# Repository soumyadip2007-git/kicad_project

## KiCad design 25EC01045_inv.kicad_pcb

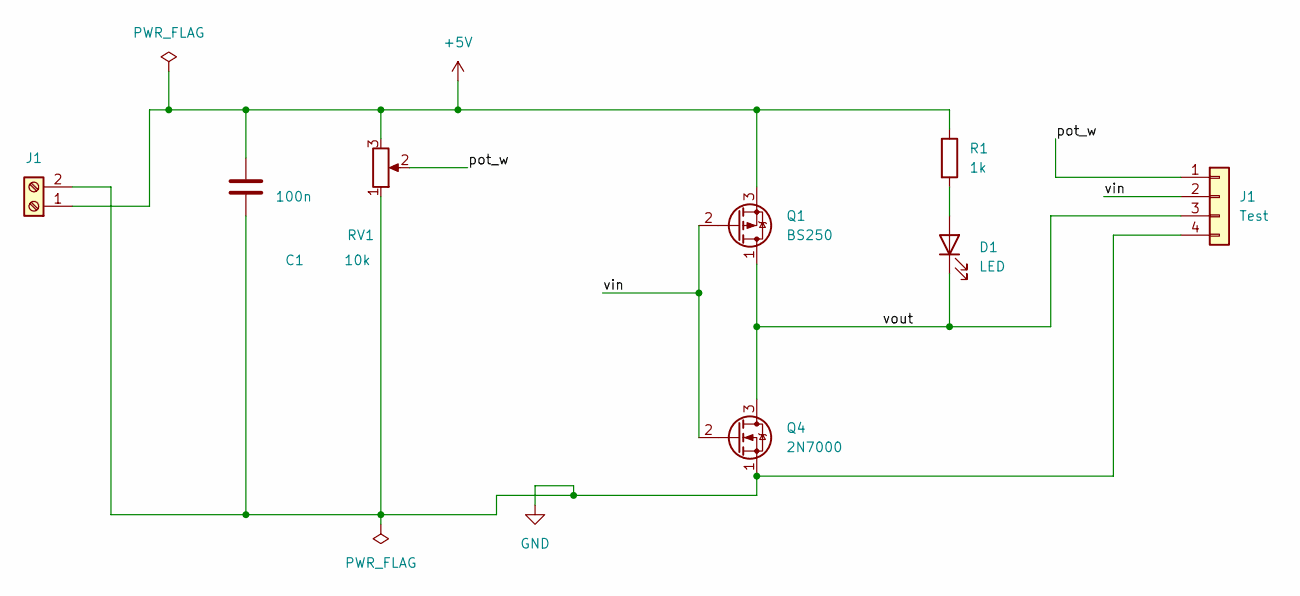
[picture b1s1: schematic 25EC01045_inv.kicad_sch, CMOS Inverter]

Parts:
C1: 100n; C_Disc_D5.0mm_W2.5mm_P5.00mm
D1: LED; LED_D3.0mm
J1: Test; PinHeader_1x04_P2.54mm_Vertical
J2: J1; TerminalBlock_Phoenix_MKDS-1,5-2-5.08_1x02_P5.08mm_Horizont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
Q1: BS250; TO-92_Inline
Q4: 2N7000; TO-92_Inline
R1: 1k; R_Axial_DIN0207_L6.3mm_D2.5mm_P10.16mm_Horizontal
RV1: 10k; Potentiometer_Bourns_3386P_Vertical

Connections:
+5V: C1.1, J2.1, Q1.3 (S), R1.1, RV1.3
/pot_w: J1.1, RV1.2
/vin: J1.2, Q1.2 (G), Q4.2 (G)
/vout: D1.1 (K), J1.3, Q1.1 (D), Q4.3 (D)
GND: C1.2, J1.4, J2.2, Q4.1 (S), RV1.1
unnamed: D1.2 (A), R1.2

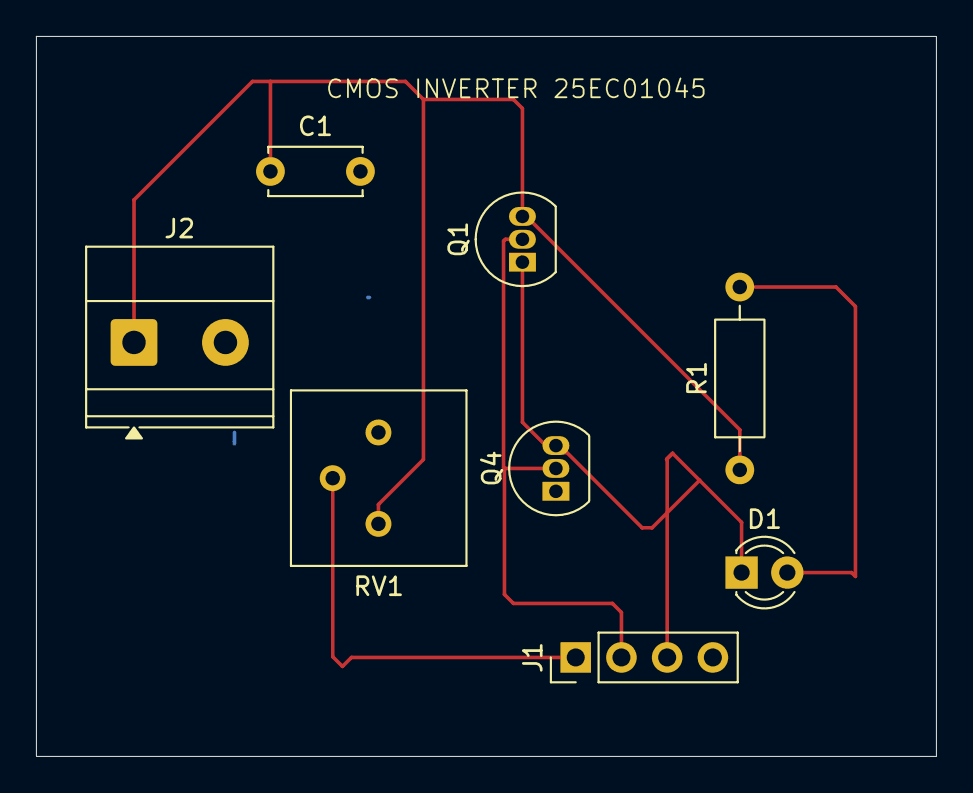
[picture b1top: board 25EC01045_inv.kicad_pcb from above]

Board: 2 copper layers, 50.0 x 40.0 mm, 8 parts (0 on the bottom side), 6 nets.
